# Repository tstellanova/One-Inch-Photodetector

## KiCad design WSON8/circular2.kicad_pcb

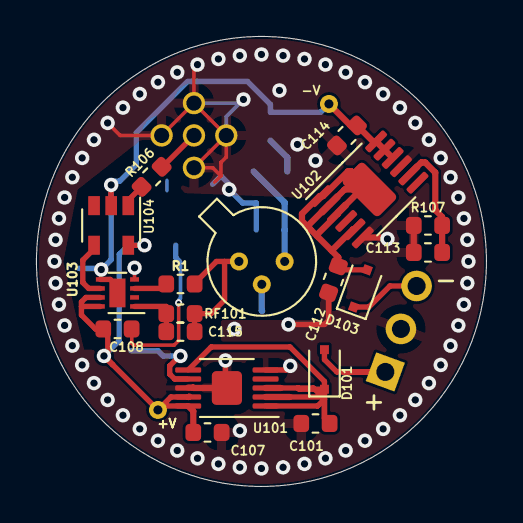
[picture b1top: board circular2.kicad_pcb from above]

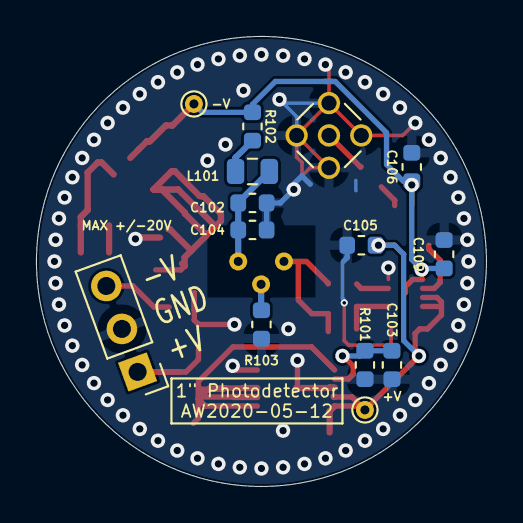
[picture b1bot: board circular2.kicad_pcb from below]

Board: 2 copper layers, 25.0 x 25.0 mm, 32 parts (14 on the bottom side), 18 nets.

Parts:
C101, C102, C103, C107, C112, C113, C114: 4u7; C_0603_1608Metric
C104: 10n; C_0603_1608Metric
C105, C106, C108, C109: 100n; C_0603_1608Metric
C115: C; C_0603_1608Metric
D101, D103: D; D_SOD-323F
D102: S597x; TO-18-3
J101: Conn_Coaxial; MMCX_Molex_73415-1471_Vertical
J102: Conn_01x03; PinHeader_1x03_P2.54mm_Vertical
L101: 100u; L_0805_2012Metric
R1: 10R; R_0603_1608Metric
R101, R107: 25k; R_0603_1608Metric
R102: 300R; R_0603_1608Metric
R103: 0R; R_0603_1608Metric
R106: 49R9; R_0603_1608Metric
RF101: R; R_0603_1608Metric
TP101, TP102: TestPoint; TestPoint_THTPad_D1.0mm_Drill0.5mm
U101: LT3042xMSE; MSOP-10-1EP_3x3mm_P0.5mm_EP1.68x1.88mm
U102: LT3093xMSE; MSOP-12-1EP_3x4mm_P0.65mm_EP1.65x2.85mm
U103: OPA859xDSG; WSON-8-1EP_2x2mm_P0.5mm_EP0.9x1.6mm
U104: BUF602xDBV; SOT-23-5

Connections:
/+V: C105.2, C107.1, C108.2, TP102.1, U101.9, U101.10, U103.7, U103.8, U104.5
/+VIN: D101.2, J102.1
/-V: C106.1, C109.1, C114.2, R102.1, TP101.1, U102.10, U102.11, U102.12, U103.5, U103.9, U104.2
/-VIN: D103.1, J102.3
/IN-: C115.2, D102.1, R1.2, RF101.2
/SET+: C103.1, R101.1, U101.7
/SET-: C113.2, R107.2, U102.8
/VBIAS: C102.1, C104.1, D102.3, L101.2
/VOUT: R106.2, U104.1
/VTIA: U103.6, U104.4
GND: C101.2, C102.2, C103.2, C104.2, C105.1, C106.2, C107.2, C108.1, C109.2, C112.1, C113.1, C114.1, J101.2, J102.2, R101.2, R103.1, R107.1, U101.5, U101.8, U101.11, U102.6, U102.9, U103.4
unnamed: C101.1, D101.1, U101.1, U101.2, U101.3, U101.6
unnamed: C112.2, D103.2, U102.1, U102.2, U102.3, U102.5, U102.13
unnamed: C115.1, RF101.1, U103.1
unnamed: D102.2, R103.2
unnamed: J101.1, R106.1
unnamed: L101.1, R102.2
unnamed: R1.1, U103.3

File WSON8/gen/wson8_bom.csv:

"Source:","/Users/toddstellanova/Documents/seti/photoboard/WSON8/circular2.kicad_sch"
"Date:","Saturday, July 02, 2022 at 05:06:42 PM"
"Tool:","Eeschema (6.0.6-0)"
"Generator:","/Applications/KiCad/KiCad.app/Contents/SharedSupport/plugins/bom_csv_grouped_by_value.py"
"Component Count:","32"

"Individual Components:"

"Item","Qty","Reference(s)","Value","LibPart","Footprint","Datasheet"
"","","C101","4u7","Device:C","Capacitor_SMD:C_0603_1608Metric","~"
"","","C102","4u7","Device:C","Capacitor_SMD:C_0603_1608Metric","~"
"","","C103","4u7","Device:C","Capacitor_SMD:C_0603_1608Metric","~"
"","","C104","10n","Device:C","Capacitor_SMD:C_0603_1608Metric","~"
"","","C105","100n","Device:C","Capacitor_SMD:C_0603_1608Metric","~"
"","","C106","100n","Device:C","Capacitor_SMD:C_0603_1608Metric","~"
"","","C107","4u7","Device:C","Capacitor_SMD:C_0603_1608Metric","~"
"","","C108","100n","Device:C","Capacitor_SMD:C_0603_1608Metric","~"
"","","C109","100n","Device:C","Capacitor_SMD:C_0603_1608Metric","~"
"","","C112","4u7","Device:C","Capacitor_SMD:C_0603_1608Metric","~"
"","","C113","4u7","Device:C","Capacitor_SMD:C_0603_1608Metric","~"
"","","C114","4u7","Device:C","Capacitor_SMD:C_0603_1608Metric","~"
"","","C115","C","Device:C","Capacitor_SMD:C_0603_1608Metric","~"
"","","D101","D","Device:D","Diode_SMD:D_SOD-323F","~"
"","","D102","S597x","Sensor_Optical:S5973","Package_TO_SOT_THT:TO-18-3","http://www.osram-os.com/Graphics/XPic5/00215016_0.pdf/BP%201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"
"","","D103","D","Device:D","Diode_SMD:D_SOD-323F","~"
"","","J101","Conn_Coaxial","Connector:Conn_Coaxial","Connector_Coaxial:MMCX_Molex_73415-1471_Vertical"," ~"
"","","J102","Conn_01x03","Connector_Generic:Conn_01x03","Connector_PinHeader_2.54mm:PinHeader_1x03_P2.54mm_Vertical","~"
"","","L101","100u","Device:L","Inductor_SMD:L_0805_2012Metric","~"
"","","R1","10R","Device:R","Resistor_SMD:R_0603_1608Metric","~"
"","","R101","25k","Device:R","Resistor_SMD:R_0603_1608Metric","~"
"","","R102","300R","Device:R","Resistor_SMD:R_0603_1608Metric","~"
"","","R103","0R","Device:R","Resistor_SMD:R_0603_1608Metric","~"
"","","R106","49R9","Device:R","Resistor_SMD:R_0603_1608Metric","~"
"","","R107","25k","Device:R","Resistor_SMD:R_0603_1608Metric","~"
"","","RF101","R","Device:R","Resistor_SMD:R_0603_1608Metric","~"
"","","TP101","TestPoint","Connector:TestPoint","TestPoint:TestPoint_THTPad_D1.0mm_Drill0.5mm","~"
"","","TP102","TestPoint","Connector:TestPoint","TestPoint:TestPoint_THTPad_D1.0mm_Drill0.5mm","~"
"","","U101","LT3042xMSE","Regulator_Linear:LT3042xMSE","Package_SO:MSOP-10-1EP_3x3mm_P0.5mm_EP1.68x1.88mm","https://www.analog.com/media/en/technical-documentation/data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"
"","","U102","LT3093xMSE","Regulator_Linear:LT3093xMSE","Package_SO:MSOP-12-1EP_3x4mm_P0.65mm_EP1.65x2.85mm","https://www.analog.com/media/en/technical-documentation/data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"
"","","U103","OPA859xDSG","Amplifier_Operational:OPA859xDSG","Package_SON:WSON-8-1EP_2x2mm_P0.5mm_EP0.9x1.6mm","http://www.ti.com/lit/ds/symlink/opa859.pdf"
"","","U104","BUF602xDBV","Amplifier_Buffer:BUF602xDBV","Package_TO_SOT_SMD:SOT-23-5","http://www.ti.com/lit/ds/symlink/buf602.pdf"



"Collated Components:"

"Item","Qty","Reference(s)","Value","LibPart","Footprint","Datasheet"
"1","7","C101, C102, C103, C107, C112, C113, C114","4u7","Device:C","Capacitor_SMD:C_0603_1608Metric","~"
"2","1","C104","10n","Device:C","Capacitor_SMD:C_0603_1608Metric","~"
"3","4","C105, C106, C108, C109","100n","Device:C","Capacitor_SMD:C_0603_1608Metric","~"
"4","1","C115","C","Device:C","Capacitor_SMD:C_0603_1608Metric","~"
"5","2","D101, D103","D","Device:D","Diode_SMD:D_SOD-323F","~"
"6","1","D102","S597x","Sensor_Optical:S5973","Package_TO_SOT_THT:TO-18-3","http://www.osram-os.com/Graphics/XPic5/00215016_0.pdf/BP%201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"
"7","1","J101","Conn_Coaxial","Connector:Conn_Coaxial","Connector_Coaxial:MMCX_Molex_73415-1471_Vertical"," ~"
"8","1","J102","Conn_01x03","Connector_Generic:Conn_01x03","Connector_PinHeader_2.54mm:PinHeader_1x03_P2.54mm_Vertical","~"
"9","1","L101","100u","Device:L","Inductor_SMD:L_0805_2012Metric","~"
"10","1","R1","10R","Device:R","Resistor_SMD:R_0603_1608Metric","~"
"11","2","R101, R107","25k","Device:R","Resistor_SMD:R_0603_1608Metric","~"
"12","1","R102","300R","Device:R","Resistor_SMD:R_0603_1608Metric","~"
"13","1","R103","0R","Device:R","Resistor_SMD:R_0603_1608Metric","~"
"14","1","R106","49R9","Device:R","Resistor_SMD:R_0603_1608Metric","~"
"15","1","RF101","R","Device:R","Resistor_SMD:R_0603_1608Metric","~"
"16","2","TP101, TP102","TestPoint","Connector:TestPoint","TestPoint:TestPoint_THTPad_D1.0mm_Drill0.5mm","~"
"17","1","U101","LT3042xMSE","Regulator_Linear:LT3042xMSE","Package_SO:MSOP-10-1EP_3x3mm_P0.5mm_EP1.68x1.88mm","https://www.analog.com/media/en/technical-documentation/data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"
"18","1","U102","LT3093xMSE","Regulator_Linear:LT3093xMSE","Package_SO:MSOP-12-1EP_3x4mm_P0.65mm_EP1.65x2.85mm","https://www.analog.com/media/en/technical-documentation/data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"
"19","1","U103","OPA859xDSG","Amplifier_Operational:OPA859xDSG","Package_SON:WSON-8-1EP_2x2mm_P0.5mm_EP0.9x1.6mm","http://www.ti.com/lit/ds/symlink/opa859.pdf"
"20","1","U104","BUF602xDBV","Amplifier_Buffer:BUF602xDBV","Package_TO_SOT_SMD:SOT-23-5","http://www.ti.com/lit/ds/symlink/buf602.pdf"

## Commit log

2022-07-05 prep for OPA858 build
2022-07-05 add CERN OHL v1.2 license

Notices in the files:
WSON8/circular2.kicad_pcb:
Copyright Anders E E Wallin, 2020.
This documentation describes Open Hardware and is licensed under the
CERN OHL v. 1.2.
